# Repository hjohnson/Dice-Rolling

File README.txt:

The DigiDice is an easy to use electronic die that is powered by 2 AA batteries, and uses a hardware random number generator to replace the six standard sizes of dice used in most games (D4, D6, D8, D10, D12, D20).  

Extended Version, for official writeup:

	ÒAny one who considers arithmetical methods of producing random digits is, of course, in a state of sin.Ó Ð John Von Neumann, 1951

   When I started this project, I had several design goals in mind: I wanted it to be extremely small and easy to carry, yet have 6 buttons to ÒrollÓ each of the standard sizes of die (D4, D6, D8, D10, D12, and D20). I also wanted it to based on a Random Number Generator (RNG) implemented in hardware instead of using the built in pseudo-random number generator. As those who have been watching the Show And Tell will know, IÕm proud to say that IÕve succeeded. 
   My first step was to learn as much as I could about the Random Generation process, so I could design my own generator. I found an open source design that I was able to implement. In this design, the Zener Effect of a 1.22V Zener Diode is used to generate Avalanche noise, which is then amplified through a 2n3904 NPN transistor and a pair of high-speed Op Amps, then delivered to the Microprocessor as a digital input. The microprocessor implements a debiasing algorithm known as the Von Neumann corrector to take the input noise distribution, which could have an uneven balance of 0s and 1s, and turn it into an even distribution of 0s and 1s. When the conditions of the corrector are met, the new random bit is mixed into a 32 bit number. Since this is implemented within a timer interrupt that triggers every 32 microseconds, the random number is updated extremely quickly. If you want to learn more about the RNG support circuitry or the software, check out the source files for this project. The Hardware process is described on the Schematic, and the software process is documented within the source code.
   To check that this device worked properly, I sampled the D20 option 250 times, and performed a PearsonÕs Chi-Squared test based on the null hypothesis that the source data is uniformly distributed. Suffice it to say, it passed, and I could not reject the null hypothesis. I also borrowed the method of testing from the original designer of the RNG hardware, so if youÕd like to look at the precise statistical methods, feel free to check them out at http://tinyurl.com/diyrandomgen 
   To make the device easy to use, I selected a two-digit seven-segment display, and found small tactile momentary switches that I could use for the UI. Since I wanted this project to be as small as possible, I decided to use Surface Mount devices for the RNG components and microprocessor and put them beneath the seven-segment display, on the underside of the board. I selected the Atmega8 to keep the LED driving simple (it has enough pins to drive both digits simultaneously, to keep the input switches on as few pins as possible (IÕm using a resistor ladder, and an ADC to read the result), and to have a small package to fit within the .6Ó spaced rows of pins on the seven-segment display. Because I was able to place all of the components (besides the switches and display) on the underside of the board, the top of the device is clean and simple and the PCB is kept to 1.1Ó x 1.25Ó, small enough to easily attach it to a 2xAA battery pack. Since the batteries would run out in under 10 days due to the high (~10mA) quiescent current use of the ADC and RNG circuitry, a simple power switch is included to turn power to the whole device on and off. At one-off prices, all of the components can be bought for about $10. The PCB is small, so if you buy from Laen over at DorkbotPDX (Who, by the way, awesomely accepted several last-minute design file changes, on a weekend no less) itÕs about $7 for 3 boards. 
   In short, this is a simple, easy to use artificial die. When a button is pressed, the machine generates a random number in the appropriate range, displays it on the screen for several seconds, and then turns off the display. If you use this device, you donÕt have to worry about carrying around a bag of dice, finding an even rolling surface, or losing a die. And in the process, I learned about Hardware RNGs, and designed my first mostly surface-mount PCB. This project is released as Open Hardware under the CC BY/SA License.

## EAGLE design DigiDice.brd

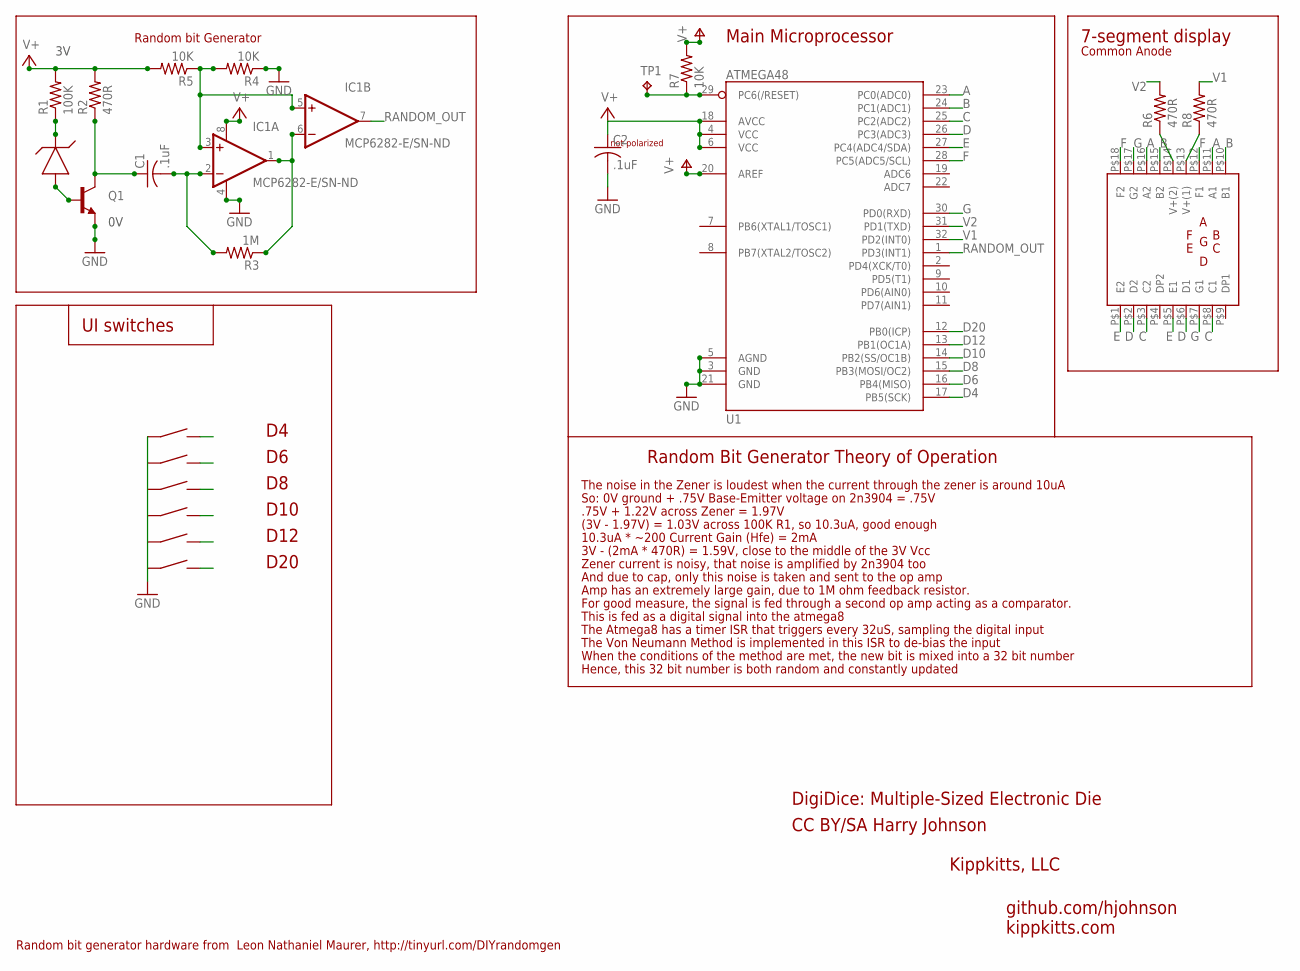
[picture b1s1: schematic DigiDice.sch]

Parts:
C1, C2: .1uF; C0805
IC1: MCP6282-E/SN-ND; SO08
Q1: TRANSISTOR_NPNSOT23; SOT23
R1: 100K; R0805
R2, R6, R8: 470R; R0805
R3: 1M; R0805
R4, R5, R7: 10K; R0805
SW1, SW2, SW3, SW4, SW5, SW6: SPST_SWITCH; EG2513-ND
TP1: TPB1,27; B1,27
U1: ATMEGA48; TQFP32-08
U$1: ZXRE1004FFTA; SOT23
U$2: 2DIGIT_7SEGMENT; HDSP-521E

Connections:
/RES: R7.1, TP1.TP, U1.29 (PC6(/RESET))
A: U1.23 (PC0(ADC0)), U$2.P$11 (A1), U$2.P$16 (A2)
B: U1.24 (PC1(ADC1)), U$2.P$10 (B1), U$2.P$15 (B2)
C: U1.25 (PC2(ADC2)), U$2.P$3 (C2), U$2.P$8 (C1)
D: U1.26 (PC3(ADC3)), U$2.P$2 (D2), U$2.P$6 (D1)
D4: SW1.P$2 (2), U1.17 (PB5(SCK))
D6: SW2.P$2 (2), U1.16 (PB4(MISO))
D8: SW3.P$2 (2), U1.15 (PB3(MOSI/OC2))
D10: SW4.P$2 (2), U1.14 (PB2(SS/OC1B))
D12: SW5.P$2 (2), U1.13 (PB1(OC1A))
D20: SW6.P$2 (2), U1.12 (PB0(ICP))
E: U1.27 (PC4(ADC4/SDA)), U$2.P$1 (E2), U$2.P$5 (E1)
F: U1.28 (PC5(ADC5/SCL)), U$2.P$12 (F1), U$2.P$18 (F2)
G: U1.30 (PD0(RXD)), U$2.P$7 (G1), U$2.P$17 (G2)
GND: C2.2, IC1.4 (V-), Q1.2 (E), R4.1, SW1.P$1 (1), SW2.P$1 (1), SW3.P$1 (1), SW4.P$1 (1), SW5.P$1 (1), SW6.P$1 (1), U1.3 (GND), U1.5 (AGND), U1.21 (GND)
unnamed: Q1.1 (B), U$1.2 (A)
unnamed: C1.1, Q1.3 (C), R2.1
unnamed: R1.1, U$1.1 (K)
unnamed: C1.2, IC1.2 (-IN), R3.2
unnamed: IC1.1 (OUT), IC1.6 (-IN), R3.1
unnamed: IC1.3 (+IN), IC1.5 (+IN), R4.2, R5.1
RANDOM_OUT: IC1.7 (OUT), U1.1 (PD3(INT1))
V1: R8.2, U1.32 (PD2(INT0))
V1_LED: R8.1, U$2.P$13 (V+(1))
V2: R6.2, U1.31 (PD1(TXD))
V2_LED: R6.1, U$2.P$14 (V+(2))
V+: C2.1, IC1.8 (V+), R1.2, R2.2, R5.2, R7.2, U1.4 (VCC), U1.6 (VCC), U1.18 (AVCC), U1.20 (AREF)

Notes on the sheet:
Random bit Generator
UI switches
7-segment display
Main Microprocessor
D10
D12
D20
Random bit generator hardware from Leon Nathaniel Maurer, http://tinyurl.com/DIYrandomgen
not polarized
DigiDice: Multiple-Sized Electronic Die
CC BY/SA Harry Johnson
github.com/hjohnson
Random Bit Generator Theory of Operation
The noise in the Zener is loudest when the current through the zener is around 10uA
So: 0V ground + .75V Base-Emitter voltage on 2n3904 = .75V
.75V + 1.22V across Zener = 1.97V
(3V - 1.97V) = 1.03V across 100K R1, so 10.3uA, good enough
10.3uA * ~200 Current Gain (Hfe) = 2mA
3V - (2mA * 470R) = 1.59V, close to the middle of the 3V Vcc
Zener current is noisy, that noise is amplified by 2n3904 too
And due to cap, only this noise is taken and sent to the op amp
Amp has an extremely large gain, due to 1M ohm feedback resistor.
For good measure, the signal is fed through a second op amp acting as a comparator.
This is fed as a digital signal into the atmega8
The Atmega8 has a timer ISR that triggers every 32uS, sampling the digital input
The Von Neumann Method is implemented in this ISR to de-bias the input
When the conditions of the method are met, the new bit is mixed into a 32 bit number
Hence, this 32 bit number is both random and constantly updated
Common Anode
Kippkitts, LLC
kippkitts.com

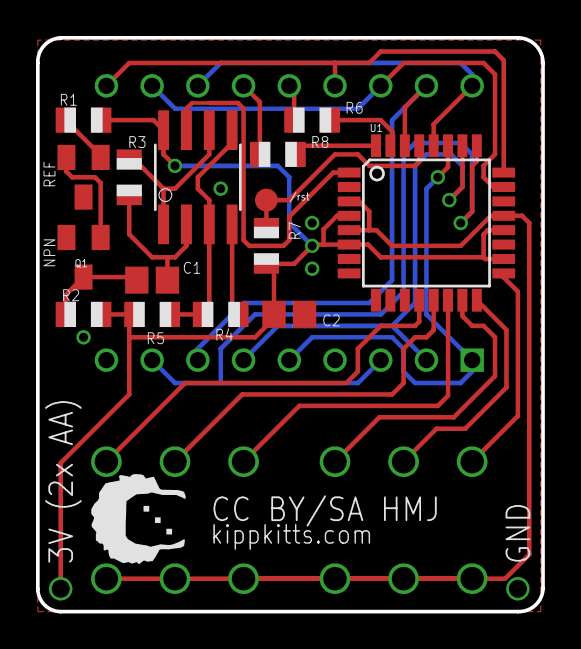
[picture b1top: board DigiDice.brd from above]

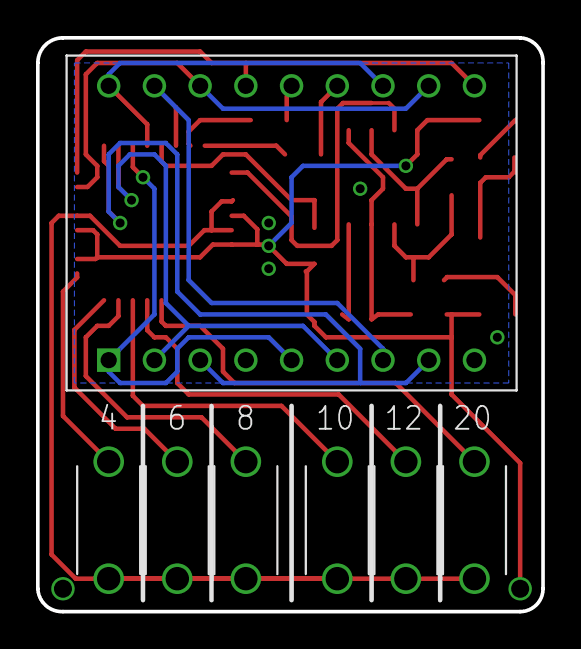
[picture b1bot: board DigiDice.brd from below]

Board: 2 copper layers, 28.1 x 31.9 mm, 23 parts (7 on the bottom side), 27 nets.

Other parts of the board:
U$4: TOP_DOCU_5MM

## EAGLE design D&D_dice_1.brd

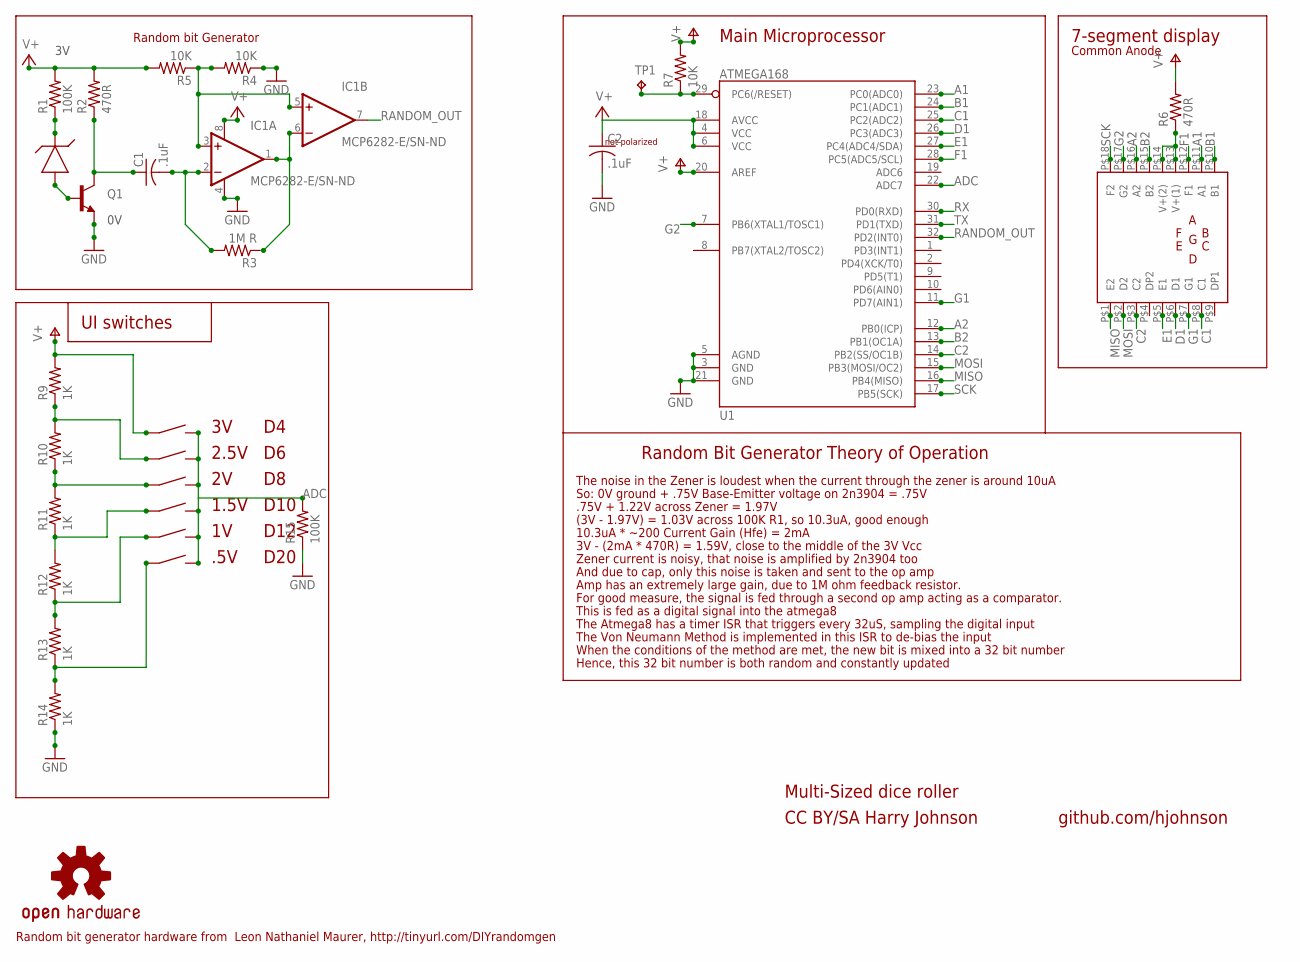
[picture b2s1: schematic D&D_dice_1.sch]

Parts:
C1, C2: .1uF; C0805
IC1: MCP6282-E/SN-ND; SO08
Q1: TRANSISTOR_NPNSOT23; SOT23
R1, R15: 100K; R0805
R2, R6: 470R; R0805
R3: 1M R; 0805
R4, R5, R7: 10K; R0805
R9, R10, R11, R12, R13, R14: 1K; R0805
SW1, SW2, SW3, SW4, SW5, SW6: SPST_SWITCH; EG2513-ND
TP1: TPB1,27; B1,27
U1: ATMEGA168; TQFP32-08
U$1: ZXRE1004FFTA; SOT23
U$2: 2DIGIT_7SEGMENT; HDSP-521E
U$3: OSHW-LOGOS; OSHW-LOGO-S

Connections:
/RES: R7.1, TP1.TP, U1.29 (PC6(/RESET))
A1: U1.23 (PC0(ADC0)), U$2.P$11 (A1)
A2: U1.12 (PB0(ICP)), U$2.P$16 (A2)
ADC: R15.2, SW1.P$2 (2), SW2.P$2 (2), SW3.P$2 (2), SW4.P$2 (2), SW5.P$2 (2), SW6.P$2 (2), U1.22 (ADC7)
B1: U1.24 (PC1(ADC1)), U$2.P$10 (B1)
B2: U1.13 (PB1(OC1A)), U$2.P$15 (B2)
C1: U1.25 (PC2(ADC2)), U$2.P$8 (C1)
C2: U1.14 (PB2(SS/OC1B)), U$2.P$3 (C2)
D1: U1.26 (PC3(ADC3)), U$2.P$6 (D1)
E1: U1.27 (PC4(ADC4/SDA)), U$2.P$5 (E1)
F1: U1.28 (PC5(ADC5/SCL)), U$2.P$12 (F1)
G1: U1.11 (PD7(AIN1)), U$2.P$7 (G1)
G2: U1.7 (PB6(XTAL1/TOSC1)), U$2.P$17 (G2)
GND: C2.2, IC1.4 (V-), Q1.2 (E), R4.1, R14.1, R15.1, U1.3 (GND), U1.5 (AGND), U1.21 (GND)
MISO: U1.16 (PB4(MISO)), U$2.P$1 (E2)
MOSI: U1.15 (PB3(MOSI/OC2)), U$2.P$2 (D2)
unnamed: Q1.1 (B), U$1.2 (A)
unnamed: C1.1, Q1.3 (C), R2.1
unnamed: R1.1, U$1.1 (K)
unnamed: C1.2, IC1.2 (-IN), R3.2
unnamed: IC1.1 (OUT), IC1.6 (-IN), R3.1
unnamed: IC1.3 (+IN), IC1.5 (+IN), R4.2, R5.1
unnamed: R6.1, U$2.P$13 (V+(1)), U$2.P$14 (V+(2))
RANDOM_OUT: IC1.7 (OUT), U1.32 (PD2(INT0))
ROLL_D6: R9.1, R10.2, SW2.P$1 (1)
ROLL_D8: R10.1, R11.2, SW3.P$1 (1)
ROLL_D10: R11.1, R12.2, SW4.P$1 (1)
ROLL_D12: R12.1, R13.2, SW5.P$1 (1)
ROLL_D20: R13.1, R14.2, SW6.P$1 (1)
RX: U1.30 (PD0(RXD))
SCK: U1.17 (PB5(SCK)), U$2.P$18 (F2)
TX: U1.31 (PD1(TXD))
V+: C2.1, IC1.8 (V+), R1.2, R2.2, R5.2, R6.2, R7.2, R9.2, SW1.P$1 (1), U1.4 (VCC), U1.6 (VCC), U1.18 (AVCC), U1.20 (AREF)

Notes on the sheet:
Random bit Generator
UI switches
2.5V
1.5V
.5V
7-segment display
Main Microprocessor
D10
D12
D20
Random bit generator hardware from Leon Nathaniel Maurer, http://tinyurl.com/DIYrandomgen
not polarized
Multi-Sized dice roller
CC BY/SA Harry Johnson
github.com/hjohnson
Random Bit Generator Theory of Operation
The noise in the Zener is loudest when the current through the zener is around 10uA
So: 0V ground + .75V Base-Emitter voltage on 2n3904 = .75V
.75V + 1.22V across Zener = 1.97V
(3V - 1.97V) = 1.03V across 100K R1, so 10.3uA, good enough
10.3uA * ~200 Current Gain (Hfe) = 2mA
3V - (2mA * 470R) = 1.59V, close to the middle of the 3V Vcc
Zener current is noisy, that noise is amplified by 2n3904 too
And due to cap, only this noise is taken and sent to the op amp
Amp has an extremely large gain, due to 1M ohm feedback resistor.
For good measure, the signal is fed through a second op amp acting as a comparator.
This is fed as a digital signal into the atmega8
The Atmega8 has a timer ISR that triggers every 32uS, sampling the digital input
The Von Neumann Method is implemented in this ISR to de-bias the input
When the conditions of the method are met, the new bit is mixed into a 32 bit number
Hence, this 32 bit number is both random and constantly updated
Common Anode

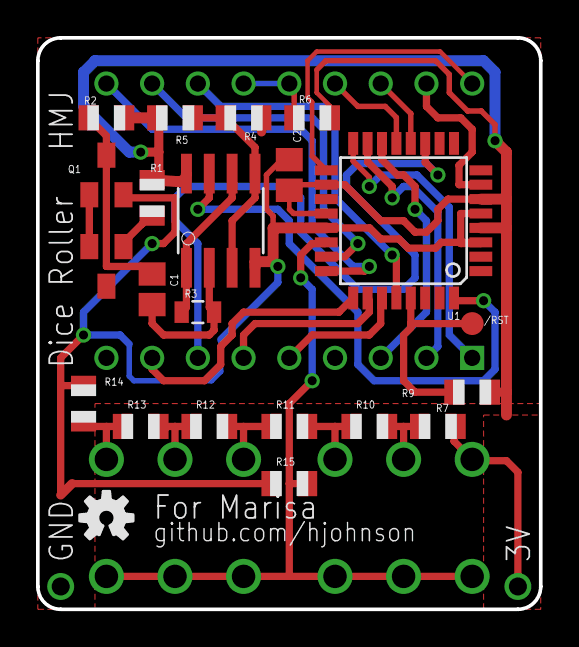
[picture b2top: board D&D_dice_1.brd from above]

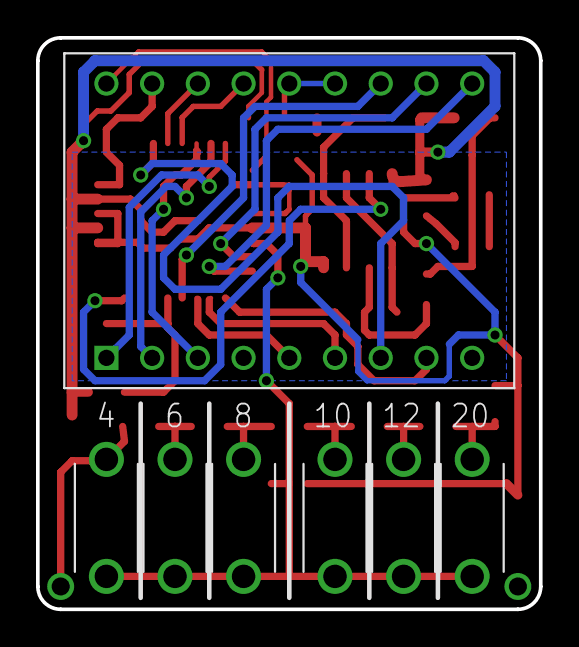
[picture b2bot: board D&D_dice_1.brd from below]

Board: 2 copper layers, 27.9 x 31.8 mm, 29 parts (7 on the bottom side), 31 nets.

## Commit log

2012-02-12 UNTESTED: Rolling of multiple different size of dice, output on a 2-digit seven segment display.
    Board, schematic, and firmware. All currently untested.
2012-02-19 Board, code improvement.
    Optimized the code, and improved the board a bit.
2012-03-03 Major commit: TESTED
    Boards re-jiggered with bigger 0805 pads, because the small ones were
    nightmarish. Code also much improved: It now actually works!
2012-03-03 Slight tweaks to the board to make it easier to solder.
2012-03-25 Added test pads for reset, lightly shifted around a few resistors.
2012-03-26 Added a whole bunch of explanatory text to the schematic.
    Theory of operation, mainly.
2012-03-26 Rotated a capacitor to make schematic look better, and added the schematic pdf.
2012-03-26 Added schematic jpeg.
2012-03-29 Added README file, copying writeup on Adafruit.com
2012-05-10 MAJOR COMMIT: New Version of Project
    Officially Renamed to DigiDice, produced by kippkitts (kippkitts.com)
    Changed board layout to remove need for power switch, hearty change in
    code to accompany, now only 2.4-2.8mA quiescent.

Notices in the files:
DigiDice.brd:
CC BY/SA HMJ
parts and their libraries:
SparkFun: Licensing: CC v3.0 Share-Alike You are welcome to use this library for commercial purposes.
